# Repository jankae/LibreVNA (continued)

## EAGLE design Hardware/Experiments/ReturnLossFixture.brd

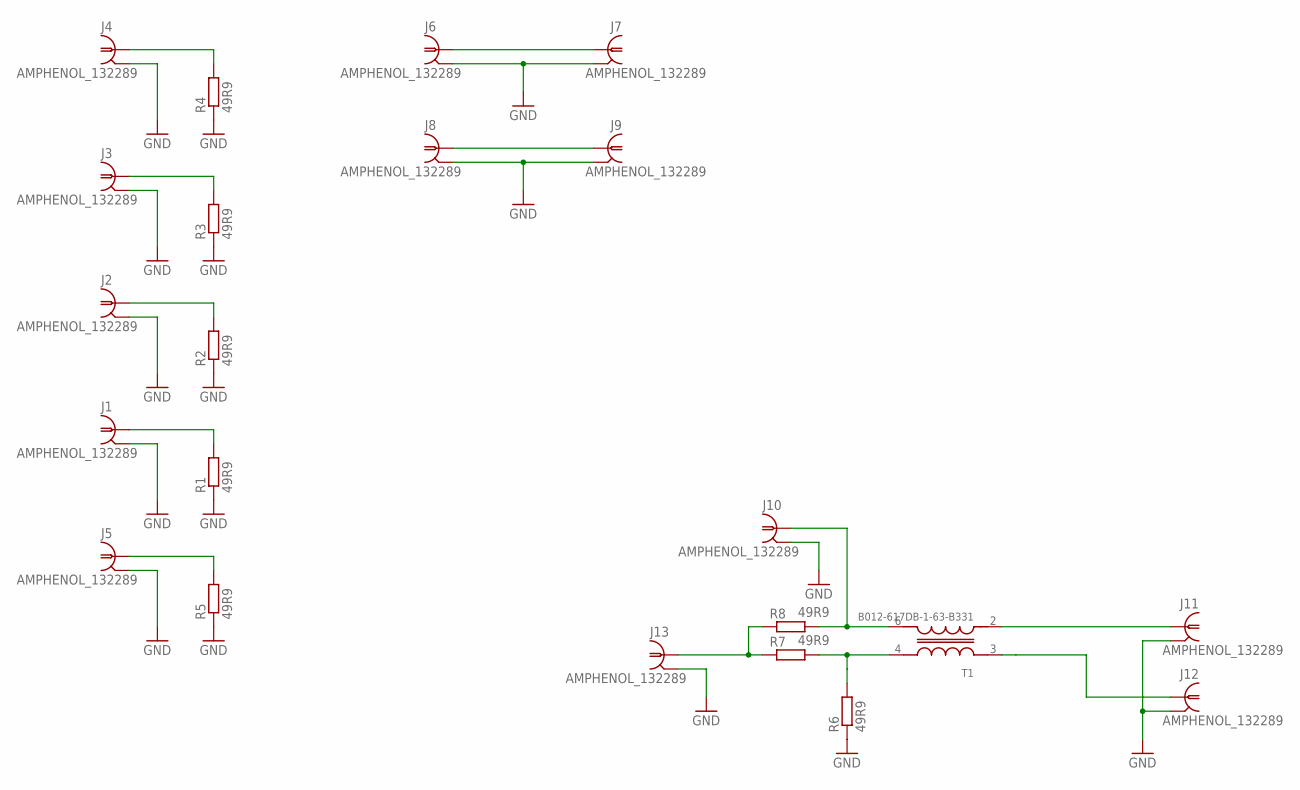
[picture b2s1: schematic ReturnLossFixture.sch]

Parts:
J1, J2, J3, J4, J5, J6, J7, J8, J9, J10, J11, J12, J13: AMPHENOL_132289
R1, R2, R3, R4, R5, R6, R7, R8: 49R9; R0402
T1: B012-617DB-1-63-B331; EASTEVER_BALUN

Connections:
GND: J1.G@1 (2), J1.G@2 (2), J1.G@3 (2), J1.G@4 (2), J2.G@1 (2), J2.G@2 (2), J2.G@3 (2), J2.G@4 (2), J3.G@1 (2), J3.G@2 (2), J3.G@3 (2), J3.G@4 (2), J4.G@1 (2), J4.G@2 (2), J4.G@3 (2), J4.G@4 (2), J5.G@1 (2), J5.G@2 (2), J5.G@3 (2), J5.G@4 (2), J6.G@1 (2), J6.G@2 (2), J6.G@3 (2), J6.G@4 (2), J7.G@1 (2), J7.G@2 (2), J7.G@3 (2), J7.G@4 (2), J8.G@1 (2), J8.G@2 (2), J8.G@3 (2), J8.G@4 (2), J9.G@1 (2), J9.G@2 (2), J9.G@3 (2), J9.G@4 (2), J10.G@1 (2), J10.G@2 (2), J10.G@3 (2), J10.G@4 (2), J11.G@1 (2), J11.G@2 (2), J11.G@3 (2), J11.G@4 (2), J12.G@1 (2), J12.G@2 (2), J12.G@3 (2), J12.G@4 (2), J13.G@1 (2), J13.G@2 (2), J13.G@3 (2), J13.G@4 (2), R1.1, R2.1, R3.1, R4.1, R5.1, R6.1
unnamed: J1.1, R1.2
unnamed: J2.1, R2.2
unnamed: J3.1, R3.2
unnamed: J4.1, R4.2
unnamed: J5.1, R5.2
unnamed: J6.1, J7.1
unnamed: J10.1, R8.2, T1.6 (OUT-)
unnamed: J8.1, J9.1
unnamed: J12.1, T1.3 (IN+)
unnamed: J11.1, T1.2 (IN-)
unnamed: R6.2, R7.2, T1.4 (OUT+)
unnamed: J13.1, R7.1, R8.1

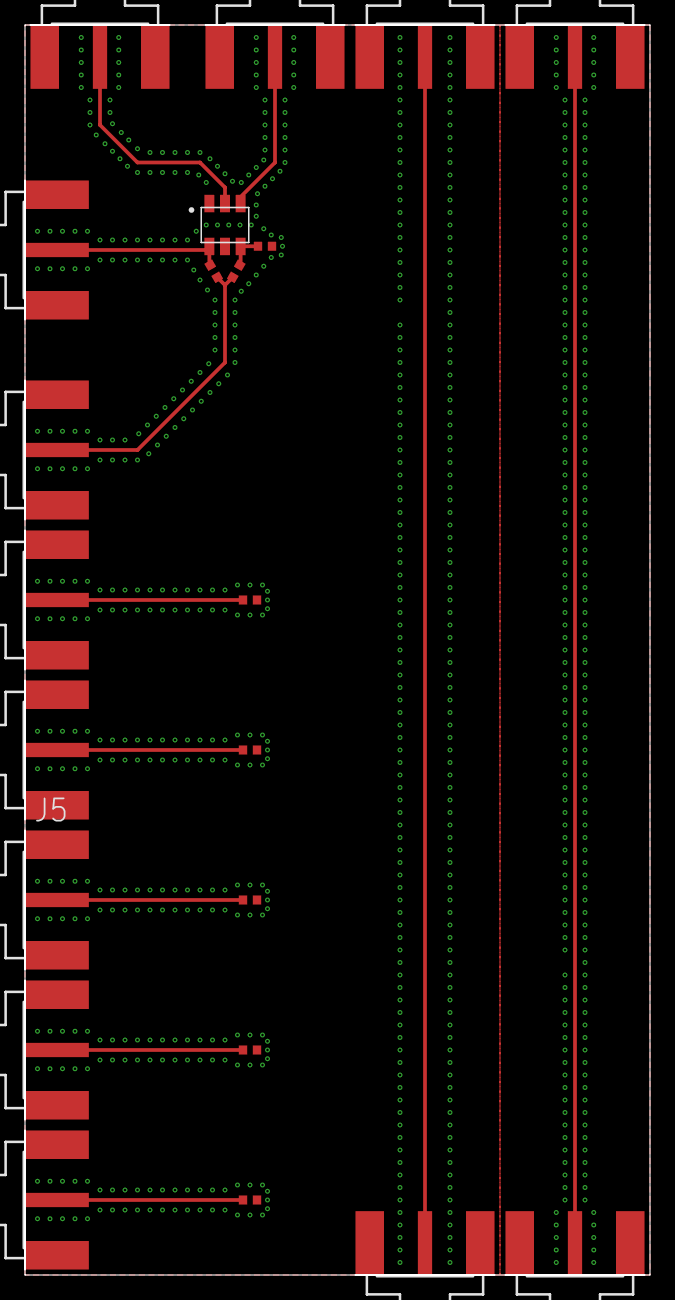
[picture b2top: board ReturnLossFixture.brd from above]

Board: 4 copper layers, 50.0 x 100.0 mm, 22 parts (0 on the bottom side), 13 nets.

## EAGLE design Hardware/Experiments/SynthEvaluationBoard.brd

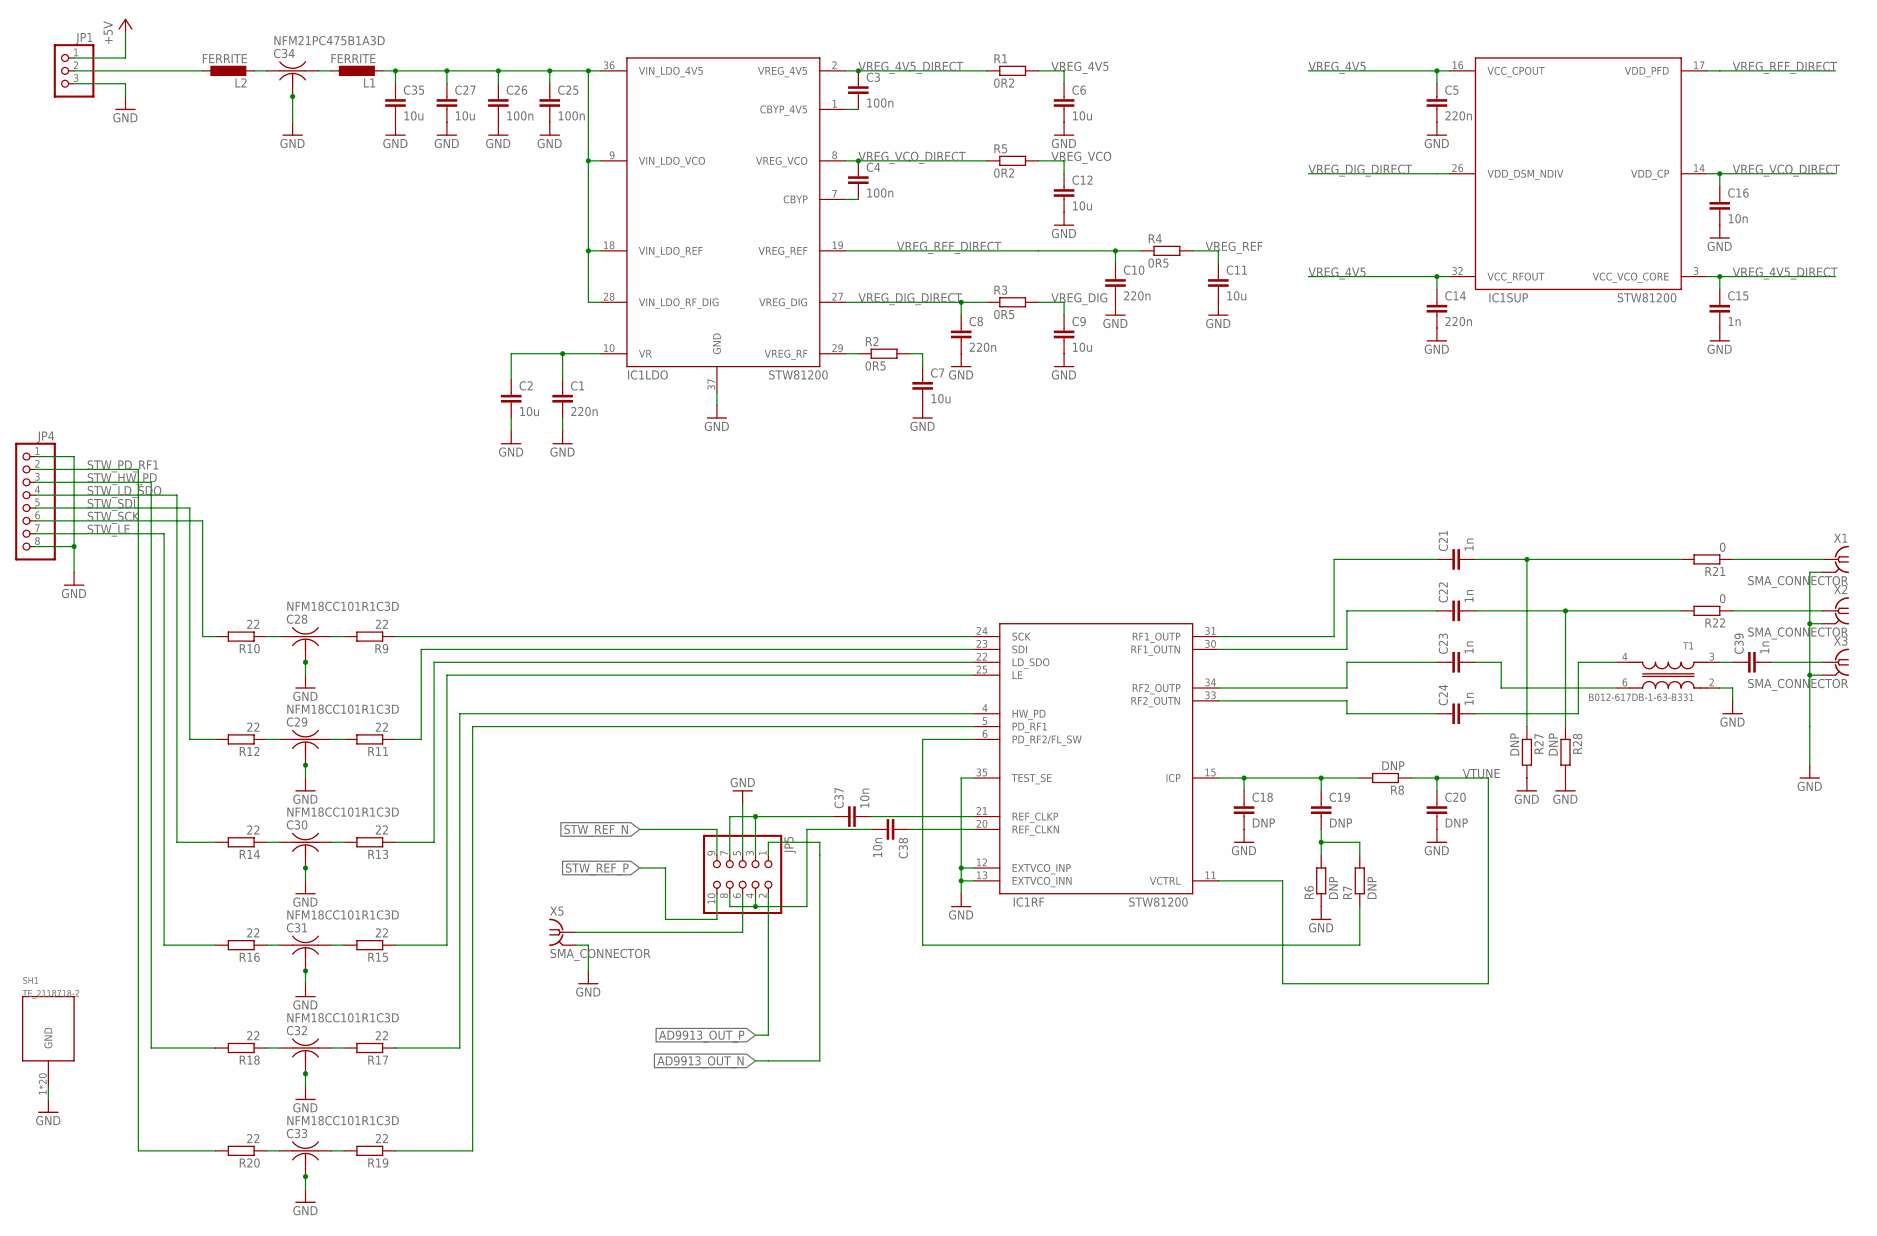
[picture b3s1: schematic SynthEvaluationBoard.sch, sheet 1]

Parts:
C1, C5, C8, C10, C14: 220n; C0402
C2, C6, C7, C9, C11, C12, C27, C35: 10u; C0603
C3, C4, C25, C26: 100n; C0402
C15, C21, C22, C23, C24, C39: 1n; C0402
C16, C37, C38: 10n; C0402
C18, C19, C20: DNP; C0402
C28, C29, C30, C31, C32, C33: NFM18CC101R1C3D; NFM18PC
C34: NFM21PC475B1A3D; NFM21PC
IC1: STW81200; QFN50P600X600X100-37T410N
JP1: PINHD-1X3; 1X03
JP4: PINHD-1X8; 1X08
JP5: PINHD-2X5; 2X05
L1, L2: FERRITE; R0402
R1, R5: 0R2; R0402
R2, R3, R4: 0R5; R0402
R6, R7, R8, R27, R28: DNP; R0402
R9, R10, R11, R12, R13, R14, R15, R16, R17, R18, R19, R20: 22; R0402
R21, R22: 0; R0402
SH1: TE_2118718-2
T1: B012-617DB-1-63-B331; EASTEVER_BALUN
X1, X2, X3, X5: SMA_CONNECTOR; J502-ND-142-0711-821/826

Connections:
+5V: JP1.1; also elsewhere on the board
AD9913_OUT_N: JP5.1; also elsewhere on the board
AD9913_OUT_P: JP5.2; also elsewhere on the board
GND: C1.2, C2.2, C5.2, C6.2, C7.2, C8.2, C9.2, C10.2, C11.2, C12.2, C14.2, C15.2, C16.2, C18.2, C20.2, C25.2, C26.2, C27.2, C28.2, C28.4 (2), C29.2, C29.4 (2), C30.2, C30.4 (2), C31.2, C31.4 (2), C32.2, C32.4 (2), C33.2, C33.4 (2), C34.2, C34.4 (2), C35.2, IC1.12 (EXTVCO_INP), IC1.13 (EXTVCO_INN), IC1.35 (TEST_SE), IC1.37 (GND), JP1.3, JP4.1, JP4.8, JP5.5, R6.1, R27.2, R28.2, SH1.1, SH1.2, SH1.3, SH1.4, SH1.5, SH1.6, SH1.7, SH1.8, SH1.9, SH1.10, SH1.11, SH1.12, SH1.13, SH1.14, SH1.15, SH1.16, SH1.17, SH1.18, SH1.19, SH1.20, T1.2 (IN-), X1.G@1 (2), X1.G@2 (2), X1.G@3 (2), X1.G@4 (2), X2.G@1 (2), X2.G@2 (2), X2.G@3 (2), X2.G@4 (2), X3.G@1 (2), X3.G@2 (2), X3.G@3 (2), X3.G@4 (2), X5.G@1 (2), X5.G@2 (2), X5.G@3 (2), X5.G@4 (2); also elsewhere on the board
unnamed: C1.1, C2.1, IC1.10 (VR)
unnamed: IC1.6 (PD_RF2/FL_SW), R7.1
unnamed: C4.2, IC1.7 (CBYP)
unnamed: C3.2, IC1.1 (CBYP_4V5)
unnamed: C19.2, R6.2, R7.2
unnamed: C18.1, C19.1, IC1.15 (ICP), R8.2
unnamed: C25.1, C26.1, C27.1, C35.1, IC1.9 (VIN_LDO_VCO), IC1.18 (VIN_LDO_REF), IC1.28 (VIN_LDO_RF_DIG), IC1.36 (VIN_LDO_4V5), L1.2
unnamed: IC1.29 (VREG_RF), R2.1
unnamed: C7.1, R2.2
unnamed: C23.1, IC1.34 (RF2_OUTP)
unnamed: C24.1, IC1.33 (RF2_OUTN)
unnamed: C22.1, IC1.30 (RF1_OUTN)
unnamed: C21.1, IC1.31 (RF1_OUTP)
unnamed: C28.1, R10.1
unnamed: C28.3, R9.2
unnamed: C29.1, R12.1
unnamed: C29.3, R11.2
unnamed: C30.1, R14.1
unnamed: C30.3, R13.2
unnamed: C31.1, R16.1
unnamed: C31.3, R15.2
unnamed: C32.1, R18.1
unnamed: C32.3, R17.2
unnamed: C33.1, R20.1
unnamed: C33.3, R19.2
unnamed: IC1.24 (SCK), R9.1
unnamed: IC1.23 (SDI), R11.1
unnamed: IC1.22 (LD_SDO), R13.1
unnamed: IC1.25 (LE), R15.1
unnamed: IC1.4 (HW_PD), R17.1
unnamed: IC1.5 (PD_RF1), R19.1
unnamed: C34.3, L1.1
unnamed: C34.1, L2.2
unnamed: R22.1, X2.1
unnamed: C22.2, R22.2, R28.1
unnamed: C23.2, T1.6 (OUT-)
unnamed: C39.1, T1.3 (IN+)
unnamed: C21.2, R21.2, R27.1
unnamed: R21.1, X1.1
unnamed: C39.2, X3.1
unnamed: JP5.6, X5.1
unnamed: JP1.2, L2.1
unnamed: C24.2, T1.4 (OUT+)
STW81200_CLK_N: C38.1, IC1.20 (REF_CLKN)
STW81200_CLK_P: C37.2, IC1.21 (REF_CLKP)
STW81200_C_N: C38.2, JP5.4, JP5.8
STW81200_C_P: C37.1, JP5.3, JP5.7
STW_HW_PD: JP4.3, R18.2; also elsewhere on the board
STW_LD_SDO: JP4.4, R14.2; also elsewhere on the board
STW_LE: JP4.7, R16.2; also elsewhere on the board
STW_PD_RF1: JP4.2, R20.2; also elsewhere on the board
STW_REF_N: JP5.9; also elsewhere on the board
STW_REF_P: JP5.10; also elsewhere on the board
STW_SCK: JP4.6, R10.2; also elsewhere on the board
STW_SDI: JP4.5, R12.2; also elsewhere on the board
VREG_4V5: C5.1, C6.1, C14.1, IC1.16 (VCC_CPOUT), IC1.32 (VCC_RFOUT), R1.2
VREG_4V5_DIRECT: C3.1, C15.1, IC1.2 (VREG_4V5), IC1.3 (VCC_VCO_CORE), R1.1
VREG_DIG: C9.1, R3.2
VREG_DIG_DIRECT: C8.1, IC1.26 (VDD_DSM_NDIV), IC1.27 (VREG_DIG), R3.1
VREG_REF: C11.1, R4.2
VREG_REF_DIRECT: C10.1, IC1.17 (VDD_PFD), IC1.19 (VREG_REF), R4.1
VREG_VCO: C12.1, R5.2
VREG_VCO_DIRECT: C4.1, C16.1, IC1.8 (VREG_VCO), IC1.14 (VDD_CP), R5.1
VTUNE: C20.1, IC1.11 (VCTRL), R8.1

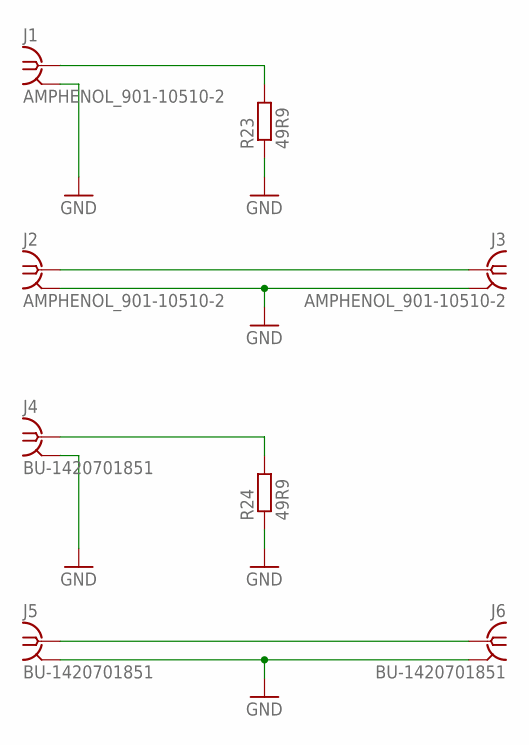
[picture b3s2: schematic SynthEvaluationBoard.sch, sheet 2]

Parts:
J1, J2, J3: AMPHENOL_901-10510-2
J4, J5, J6: BU-1420701851
R23, R24: 49R9; R0402

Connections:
GND: J1.G1 (2), J1.G2 (2), J1.G3 (2), J1.G4 (2), J2.G1 (2), J2.G2 (2), J2.G3 (2), J2.G4 (2), J3.G1 (2), J3.G2 (2), J3.G3 (2), J3.G4 (2), J4.G@1 (2), J4.G@2 (2), J4.G@3 (2), J4.G@4 (2), J5.G@1 (2), J5.G@2 (2), J5.G@3 (2), J5.G@4 (2), J6.G@1 (2), J6.G@2 (2), J6.G@3 (2), J6.G@4 (2), R23.1, R24.1; also elsewhere on the board
unnamed: J1.S (1), R23.2
unnamed: J2.S (1), J3.S (1)
unnamed: J4.1, R24.2
unnamed: J5.1, J6.1

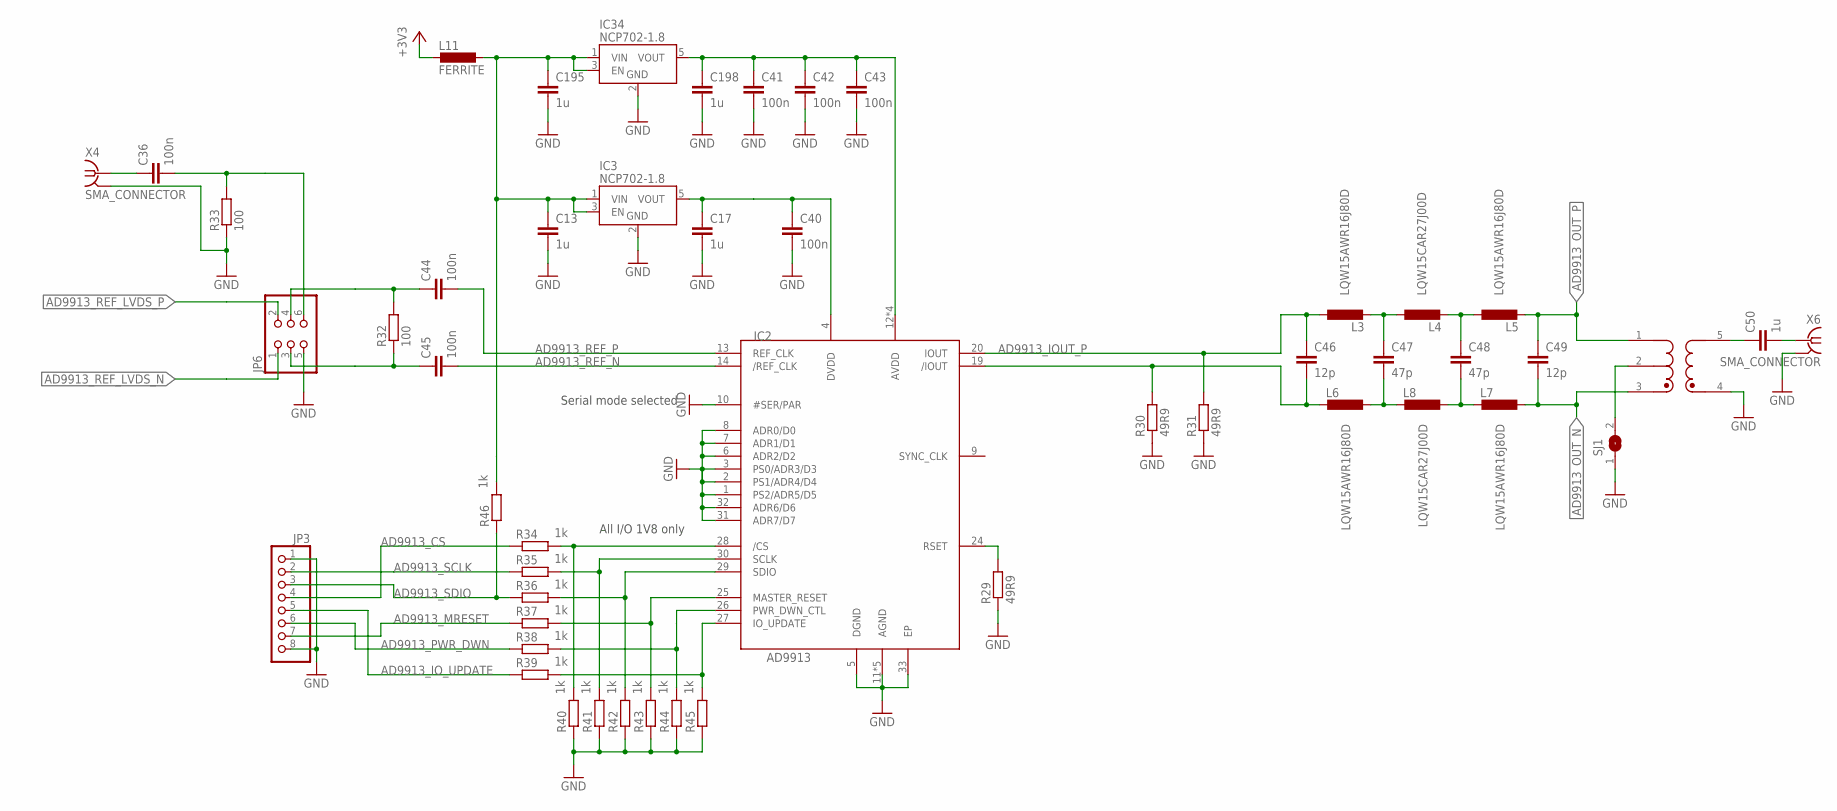
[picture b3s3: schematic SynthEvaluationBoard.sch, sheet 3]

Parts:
B1: ETC1-1T-2; SM-22
C13, C17, C50, C195, C198: 1u; C0402
C36, C40, C41, C42, C43, C44, C45: 100n; C0402
C46, C49: 12p; C0402
C47, C48: 47p; C0402
IC2: AD9913; QFN50P500X500X80-33T310
IC3, IC34: NCP702-1.8; SOT95P240X110-5
JP3: PINHD-1X8; 1X08
JP6: PINHD-2X3; 2X03
L3, L5, L6, L7: LQW15AWR16J80D; L0402
L4, L8: LQW15CAR27J00D; L0402
L11: FERRITE; R0402
R29, R30, R31: 49R9; R0402
R32, R33: 100; R0402
R34, R35, R36, R37, R38, R39, R40, R41, R42, R43, R44, R45, R46: 1k; R0402
SJ1: SJ
X4, X6: SMA_CONNECTOR; J502-ND-142-0711-821/826

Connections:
+3V3: L11.2; also elsewhere on the board
AD9913_CS: JP3.4, R34.1; also elsewhere on the board
AD9913_IOUT_N: C46.2, IC2.19 (/IOUT), L6.2, R30.2
AD9913_IOUT_P: C46.1, IC2.20 (IOUT), L3.1, R31.2
AD9913_IO_UPDATE: JP3.5, R39.1; also elsewhere on the board
AD9913_MRESET: JP3.7, R37.1; also elsewhere on the board
AD9913_OUT_N: B1.3 (SEC_DOT), C49.2, L7.1; also elsewhere on the board
AD9913_OUT_P: B1.1 (SEC), C49.1, L5.2; also elsewhere on the board
AD9913_PWR_DWN: JP3.6, R38.1; also elsewhere on the board
AD9913_REF_IN_N: C45.1, JP6.3, R32.1
AD9913_REF_IN_P: C44.1, JP6.4, R32.2
AD9913_REF_LVDS_N: JP6.1; also elsewhere on the board
AD9913_REF_LVDS_P: JP6.2; also elsewhere on the board
AD9913_REF_N: C45.2, IC2.14 (/REF_CLK)
AD9913_REF_P: C44.2, IC2.13 (REF_CLK)
AD9913_SCLK: JP3.2, R35.1; also elsewhere on the board
AD9913_SDIO: JP3.3, R36.1, R46.1; also elsewhere on the board
GND: B1.4 (PRI_DOT), C13.2, C17.2, C40.2, C41.2, C42.2, C43.2, C195.2, C198.2, IC2.1 (PS2/ADR5/D5), IC2.2 (PS1/ADR4/D4), IC2.3 (PS0/ADR3/D3), IC2.5 (DGND), IC2.6 (ADR2/D2), IC2.7 (ADR1/D1), IC2.8 (ADR0/D0), IC2.10 (#SER/PAR), IC2.11 (AGND), IC2.15 (AGND), IC2.18 (AGND), IC2.21 (AGND), IC2.23 (AGND), IC2.31 (ADR7/D7), IC2.32 (ADR6/D6), IC2.33 (EP), IC3.2 (GND), IC34.2 (GND), JP3.1, JP3.8, JP6.5, R29.1, R30.1, R31.1, R33.1, R40.1, R41.1, R42.1, R43.1, R44.1, R45.1, SJ1.1, X4.G@1 (2), X4.G@2 (2), X4.G@3 (2), X4.G@4 (2), X6.G@1 (2), X6.G@2 (2), X6.G@3 (2), X6.G@4 (2); also elsewhere on the board
unnamed: C13.1, C195.1, IC3.1 (VIN), IC3.3 (EN), IC34.1 (VIN), IC34.3 (EN), L11.1, R46.2
unnamed: C17.1, C40.1, IC2.4 (DVDD), IC3.5 (VOUT)
unnamed: IC2.24 (RSET), R29.2
unnamed: C36.2, JP6.6, R33.2
unnamed: IC2.28 (/CS), R34.2, R40.2
unnamed: IC2.30 (SCLK), R35.2, R41.2
unnamed: IC2.29 (SDIO), R36.2, R42.2
unnamed: IC2.25 (MASTER_RESET), R37.2, R43.2
unnamed: IC2.26 (PWR_DWN_CTL), R38.2, R44.2
unnamed: IC2.27 (IO_UPDATE), R39.2, R45.2
unnamed: C47.1, L3.2, L4.1
unnamed: C47.2, L6.1, L8.2
unnamed: C48.2, L7.2, L8.1
unnamed: C48.1, L4.2, L5.1
unnamed: B1.2 (SEC_CT), SJ1.2
unnamed: C50.2, X6.1
unnamed: C36.1, X4.1
unnamed: B1.5 (PRI), C50.1
unnamed: C41.1, C42.1, C43.1, C198.1, IC2.12 (AVDD), IC2.16 (AVDD), IC2.17 (AVDD), IC2.22 (AVDD), IC34.5 (VOUT)

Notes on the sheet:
Serial mode selected
All I/O 1V8 only

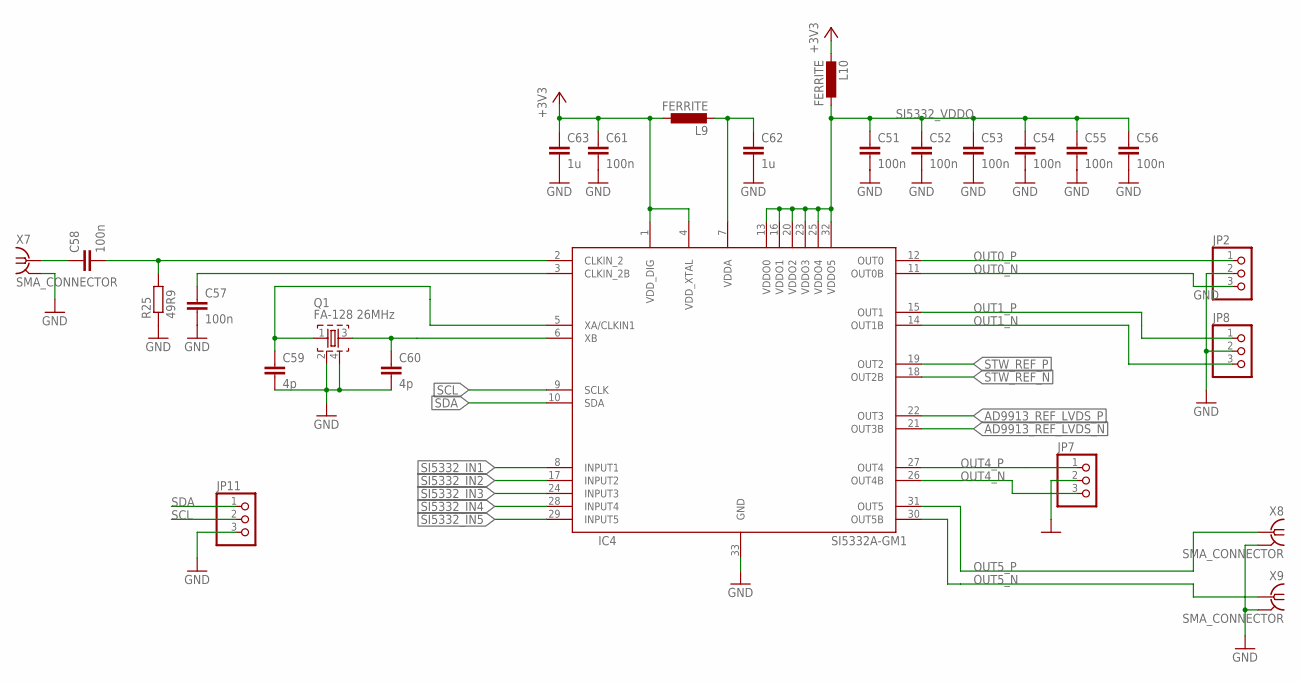
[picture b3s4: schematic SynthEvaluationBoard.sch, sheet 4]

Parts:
C51, C52, C53, C54, C55, C56, C57, C58, C61: 100n; C0402
C59, C60: 4p; C0402
C62, C63: 1u; C0402
IC4: SI5332A-GM1; QFN50P500X500X100-33T345N
JP2, JP7, JP8, JP11: PINHD-1X3; 1X03
L9, L10: FERRITE; R0402
Q1: FA-128 26MHz; FA-128
R25: 49R9; R0402
X7, X8, X9: SMA_CONNECTOR; J502-ND-142-0711-821/826

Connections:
+3V3: C61.1, C63.1, IC4.1 (VDD_DIG), IC4.4 (VDD_XTAL), L9.1, L10.2; also elsewhere on the board
AD9913_REF_LVDS_N: IC4.21 (OUT3B); also elsewhere on the board
AD9913_REF_LVDS_P: IC4.22 (OUT3); also elsewhere on the board
GND: C51.2, C52.2, C53.2, C54.2, C55.2, C56.2, C57.2, C59.2, C60.2, C61.2, C62.2, C63.2, IC4.33 (GND), JP2.2, JP7.2, JP8.2, JP11.3, Q1.2, Q1.4, R25.1, X7.G@1 (2), X7.G@2 (2), X7.G@3 (2), X7.G@4 (2), X8.G@1 (2), X8.G@2 (2), X8.G@3 (2), X8.G@4 (2), X9.G@1 (2), X9.G@2 (2), X9.G@3 (2), X9.G@4 (2); also elsewhere on the board
unnamed: C57.1, IC4.3 (CLKIN_2B)
unnamed: C58.2, IC4.2 (CLKIN_2), R25.2
unnamed: C58.1, X7.1
unnamed: C60.1, IC4.6 (XB), Q1.3
unnamed: C59.1, IC4.5 (XA/CLKIN1), Q1.1
unnamed: C62.1, IC4.7 (VDDA), L9.2
OUT0_N: IC4.11 (OUT0B), JP2.3
OUT0_P: IC4.12 (OUT0), JP2.1
OUT1_N: IC4.14 (OUT1B), JP8.3
OUT1_P: IC4.15 (OUT1), JP8.1
OUT4_N: IC4.26 (OUT4B), JP7.3
OUT4_P: IC4.27 (OUT4), JP7.1
OUT5_N: IC4.30 (OUT5B), X9.1
OUT5_P: IC4.31 (OUT5), X8.1
SCL: IC4.9 (SCLK), JP11.2; also elsewhere on the board
SDA: IC4.10 (SDA), JP11.1; also elsewhere on the board
SI5332_IN1: IC4.8 (INPUT1); also elsewhere on the board
SI5332_IN2: IC4.17 (INPUT2); also elsewhere on the board
SI5332_IN3: IC4.24 (INPUT3); also elsewhere on the board
SI5332_IN4: IC4.28 (INPUT4); also elsewhere on the board
SI5332_IN5: IC4.29 (INPUT5); also elsewhere on the board
SI5332_VDDO: C51.1, C52.1, C53.1, C54.1, C55.1, C56.1, IC4.13 (VDDO0), IC4.16 (VDDO1), IC4.20 (VDDO2), IC4.23 (VDDO3), IC4.25 (VDDO4), IC4.32 (VDDO5), L10.1
STW_REF_N: IC4.18 (OUT2B); also elsewhere on the board
STW_REF_P: IC4.19 (OUT2); also elsewhere on the board

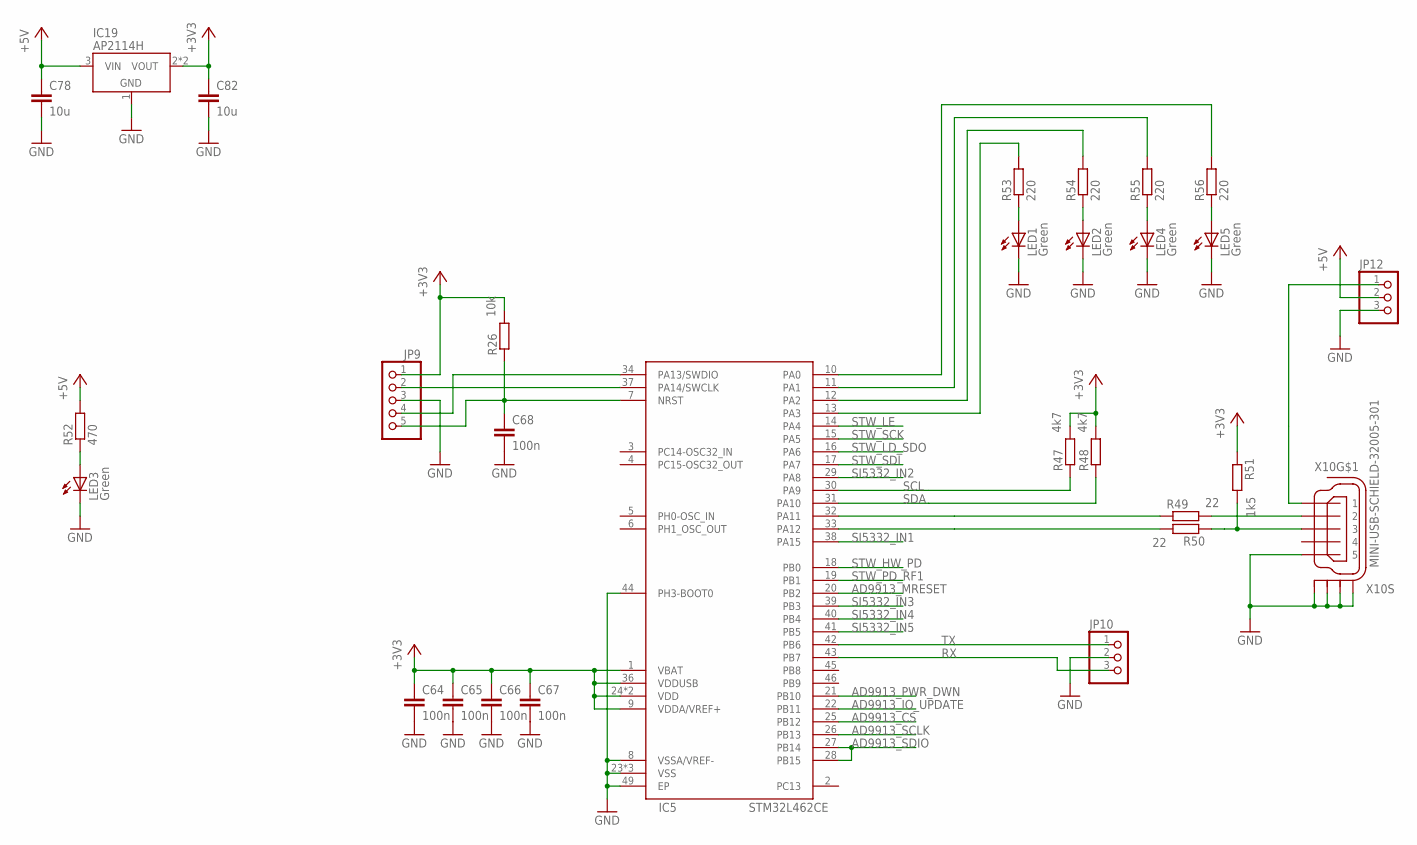
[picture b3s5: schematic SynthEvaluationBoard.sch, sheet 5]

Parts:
C64, C65, C66, C67, C68: 100n; C0402
C78, C82: 10u; C1206
IC5: STM32L462CE; QFN50P700X700X60-49T560N
IC19: AP2114H; SOT230P700X180-4
JP9: PINHD-1X5; 1X05
JP10, JP12: PINHD-1X3; 1X03
LED1, LED2, LED3, LED4, LED5: Green; LED_SML0603
R26: 10k; R0402
R47, R48: 4k7; R0402
R49, R50: 22; R0402
R51: 1k5; R0402
R52: 470; R0402
R53, R54, R55, R56: 220; R0402
X10: MINI-USB-SCHIELD-32005-301; 32005-301

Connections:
+3V3: C64.1, C65.1, C66.1, C67.1, C82.1, IC5.1 (VBAT), IC5.9 (VDDA/VREF+), IC5.24 (VDD), IC5.36 (VDDUSB), IC5.48 (VDD), IC19.2 (VOUT), IC19.4 (VOUT), JP9.1, R26.2, R47.2, R48.2, R51.1; also elsewhere on the board
+5V: C78.1, IC19.3 (VIN), JP12.2, R52.2; also elsewhere on the board
AD9913_CS: IC5.25 (PB12); also elsewhere on the board
AD9913_IO_UPDATE: IC5.22 (PB11); also elsewhere on the board
AD9913_MRESET: IC5.20 (PB2); also elsewhere on the board
AD9913_PWR_DWN: IC5.21 (PB10); also elsewhere on the board
AD9913_SCLK: IC5.26 (PB13); also elsewhere on the board
AD9913_SDIO: IC5.27 (PB14), IC5.28 (PB15); also elsewhere on the board
GND: C64.2, C65.2, C66.2, C67.2, C68.2, C78.2, C82.2, IC5.8 (VSSA/VREF-), IC5.23 (VSS), IC5.35 (VSS), IC5.44 (PH3-BOOT0), IC5.47 (VSS), IC5.49 (EP), IC19.1 (GND), JP9.3, JP10.2, JP12.3, LED1.C, LED2.C, LED3.C, LED4.C, LED5.C, X10.5, X10.M1 (S1), X10.M2 (S2), X10.M3 (S3), X10.M4 (S4); also elsewhere on the board
unnamed: LED3.A, R52.1
unnamed: JP12.1, X10.1
unnamed: LED1.A, R53.1
unnamed: LED2.A, R54.1
unnamed: LED4.A, R55.1
unnamed: IC5.37 (PA14/SWCLK), JP9.2
unnamed: IC5.34 (PA13/SWDIO), JP9.4
unnamed: C68.1, IC5.7 (NRST), JP9.5, R26.1
unnamed: LED5.A, R56.1
unnamed: IC5.13 (PA3), R53.2
unnamed: IC5.12 (PA2), R54.2
unnamed: IC5.11 (PA1), R55.2
unnamed: IC5.10 (PA0), R56.2
unnamed: R49.2, X10.2
unnamed: R50.1, R51.2, X10.3
unnamed: IC5.32 (PA11), R49.1
unnamed: IC5.33 (PA12), R50.2
RX: IC5.43 (PB7), JP10.3
SCL: IC5.30 (PA9), R47.1; also elsewhere on the board
SDA: IC5.31 (PA10), R48.1; also elsewhere on the board
SI5332_IN1: IC5.38 (PA15); also elsewhere on the board
SI5332_IN2: IC5.29 (PA8); also elsewhere on the board
SI5332_IN3: IC5.39 (PB3); also elsewhere on the board
SI5332_IN4: IC5.40 (PB4); also elsewhere on the board
SI5332_IN5: IC5.41 (PB5); also elsewhere on the board
STW_HW_PD: IC5.18 (PB0); also elsewhere on the board
STW_LD_SDO: IC5.16 (PA6); also elsewhere on the board
STW_LE: IC5.14 (PA4); also elsewhere on the board
STW_PD_RF1: IC5.19 (PB1); also elsewhere on the board
STW_SCK: IC5.15 (PA5); also elsewhere on the board
STW_SDI: IC5.17 (PA7); also elsewhere on the board
TX: IC5.42 (PB6), JP10.1

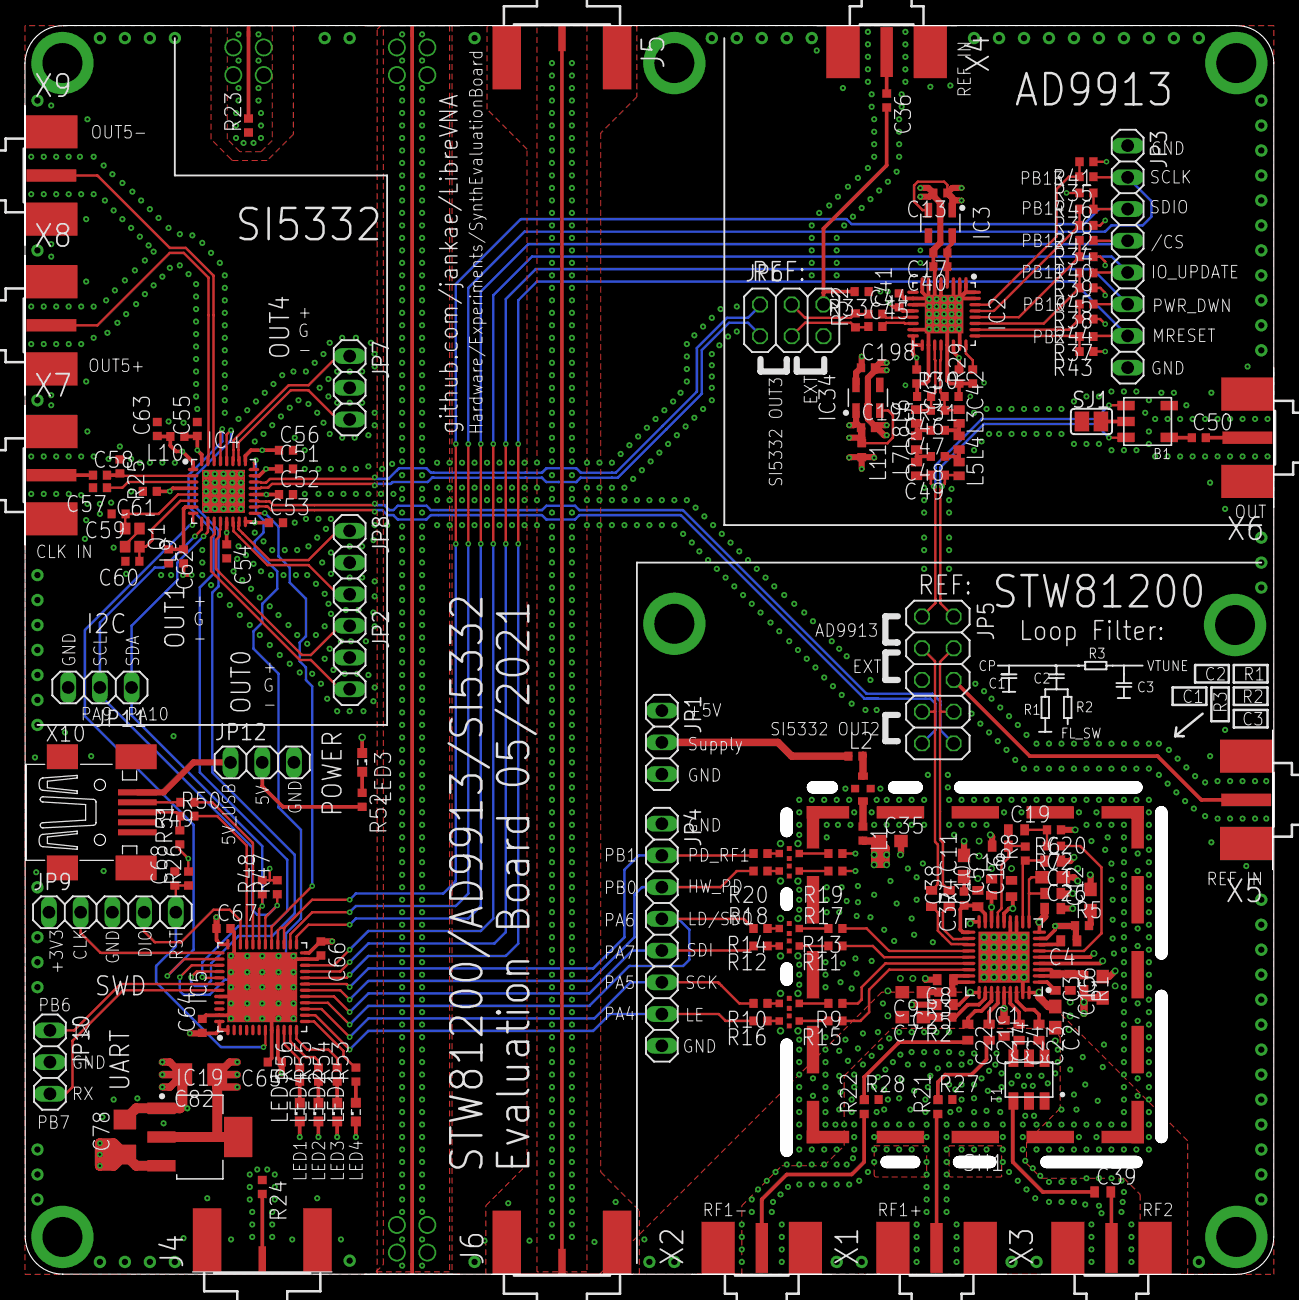
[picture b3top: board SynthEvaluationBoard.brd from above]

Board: 4 copper layers, 100.0 x 100.0 mm, 184 parts (0 on the bottom side), 147 nets.

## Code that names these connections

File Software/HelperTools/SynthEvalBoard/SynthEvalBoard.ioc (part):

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Mcu.Name=STM32L443CCUx
Mcu.Package=UFQFPN48
Mcu.UserName=STM32L443CCUx
PA0.Signal=S_TIM2_CH1
PA1.Signal=S_TIM2_CH2
PA10.Mode=I2C
PA10.Signal=I2C1_SDA
PA11.Mode=Device
PA11.Signal=USB_DM
PA12.Mode=Device
PA12.Signal=USB_DP
PA13\ (JTMS-SWDIO).Mode=Serial_Wire
PA13\ (JTMS-SWDIO).Signal=SYS_JTMS-SWDIO
PA14\ (JTCK-SWCLK).Mode=Serial_Wire
PA14\ (JTCK-SWCLK).Signal=SYS_JTCK-SWCLK
PA15\ (JTDI).GPIOParameters=GPIO_Label
PA15\ (JTDI).GPIO_Label=SI5332_IN1
PA15\ (JTDI).Signal=GPIO_Output
PA2.Signal=S_TIM2_CH3
PA3.Signal=S_TIM2_CH4
PA4.GPIOParameters=GPIO_Label
PA4.GPIO_Label=STW_LE
PA4.Signal=GPIO_Output
PA5.Mode=Full_Duplex_Master
PA5.Signal=SPI1_SCK
PA6.GPIOParameters=GPIO_PuPd
PA6.GPIO_PuPd=GPIO_PULLUP
PA6.Mode=Full_Duplex_Master
PA6.Signal=SPI1_MISO
PA7.Mode=Full_Duplex_Master
PA7.Signal=SPI1_MOSI
PA8.GPIOParameters=GPIO_Label
PA8.GPIO_Label=SI5332_IN2
PA8.Signal=GPIO_Output
PA9.Mode=I2C
PA9.Signal=I2C1_SCL
PB0.GPIOParameters=GPIO_Label
PB0.GPIO_Label=STW_HW_PD
PB0.Signal=GPIO_Output
PB1.GPIOParameters=GPIO_Label
PB1.GPIO_Label=STW_PD_RF1
PB1.Signal=GPIO_Output
PB10.GPIOParameters=GPIO_Label
PB10.GPIO_Label=AD9913_PWR_DWN
PB10.Signal=GPIO_Output
PB11.GPIOParameters=GPIO_Label
PB11.GPIO_Label=AD9913_IO_UPDATE
PB11.Signal=GPIO_Output
PB12.GPIOParameters=GPIO_Label
PB12.GPIO_Label=AD9913_CS
PB12.Signal=GPIO_Output
PB13.Mode=Full_Duplex_Master
PB13.Signal=SPI2_SCK
PB14.Mode=Full_Duplex_Master
PB14.Signal=SPI2_MISO
PB15.Mode=Full_Duplex_Master
PB15.Signal=SPI2_MOSI
PB2.GPIOParameters=GPIO_Label
PB2.GPIO_Label=AD9913_MRESET
PB2.Signal=GPIO_Output
PB3\ (JTDO-TRACESWO).GPIOParameters=GPIO_Label
PB3\ (JTDO-TRACESWO).GPIO_Label=SI5332_IN3
PB3\ (JTDO-TRACESWO).Signal=GPIO_Output
PB4\ (NJTRST).GPIOParameters=GPIO_Label
PB4\ (NJTRST).GPIO_Label=SI5332_IN4
PB4\ (NJTRST).Signal=GPIO_Output
PB5.GPIOParameters=GPIO_Label
PB5.GPIO_Label=SI5332_IN5
PB5.Signal=GPIO_Output
PB6.Mode=Asynchronous
PB6.Signal=USART1_TX
PB7.Mode=Asynchronous
PB7.Signal=USART1_RX
RCC.HSE_VALUE=8000000
RCC.SYSCLKFreq_VALUE=80000000
RCC.SYSCLKSource=RCC_SYSCLKSOURCE_PLLCLK
board=custom

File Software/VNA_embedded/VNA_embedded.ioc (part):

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Mcu.Name=STM32G431C(6-8-B)Ux
Mcu.Package=UFQFPN48
Mcu.UserName=STM32G431CBUx
PA1.GPIOParameters=GPIO_Speed,GPIO_Label
PA1.GPIO_Label=FPGA_AUX1
PA1.GPIO_Speed=GPIO_SPEED_FREQ_VERY_HIGH
PA1.Signal=GPIO_Output
PA10.Mode=EnableDeadBattery
PA10.Signal=UCPD1_DBCC2
PA11.Mode=Device
PA11.Signal=USB_DM
PA12.Mode=Device
PA12.Signal=USB_DP
PA13.Mode=Serial_Wire
PA13.Signal=SYS_JTMS-SWDIO
PA14.Mode=Serial_Wire
PA14.Signal=SYS_JTCK-SWCLK
PA15.Signal=S_TIM2_CH1
PA2.GPIOParameters=GPIO_Speed,GPIO_Label
PA2.GPIO_Label=FPGA_AUX3
PA2.GPIO_Speed=GPIO_SPEED_FREQ_VERY_HIGH
PA2.Signal=GPIO_Output
PA3.GPIOParameters=GPIO_Speed,GPIO_Label
PA3.GPIO_Label=FPGA_AUX2
PA3.GPIO_Speed=GPIO_SPEED_FREQ_VERY_HIGH
PA3.Signal=GPIO_Output
PA4.GPIOParameters=GPIO_Speed,PinState,GPIO_Label
PA4.GPIO_Label=FPGA_CS
PA4.GPIO_Speed=GPIO_SPEED_FREQ_VERY_HIGH
PA4.PinState=GPIO_PIN_SET
PA4.Signal=GPIO_Output
PA5.GPIOParameters=GPIO_Speed
PA5.GPIO_Speed=GPIO_SPEED_FREQ_VERY_HIGH
PA5.Mode=Full_Duplex_Master
PA5.Signal=SPI1_SCK
PA6.GPIOParameters=GPIO_Speed
PA6.GPIO_Speed=GPIO_SPEED_FREQ_VERY_HIGH
PA6.Mode=Full_Duplex_Master
PA6.Signal=SPI1_MISO
PA7.GPIOParameters=GPIO_Speed
PA7.GPIO_Speed=GPIO_SPEED_FREQ_VERY_HIGH
PA7.Mode=Full_Duplex_Master
PA7.Signal=SPI1_MOSI
PA8.GPIOParameters=GPIO_Pu
PA8.GPIO_Pu=GPIO_PULLUP
PA8.Mode=I2C
PA8.Signal=I2C2_SDA
PA9.Mode=EnableDeadBattery
PA9.Signal=UCPD1_DBCC1
PB0.GPIOParameters=GPIO_Speed,PinState,GPIO_Label
PB0.GPIO_Label=FLASH_CS
PB0.GPIO_Speed=GPIO_SPEED_FREQ_VERY_HIGH
PB0.PinState=GPIO_PIN_SET
PB0.Signal=GPIO_Output
PB1.GPIOParameters=GPIO_Label
PB1.GPIO_Label=FPGA_INTR
PB1.Signal=GPXTI1
PB11.Mode=Asynchronous
PB11.Signal=USART3_RX
PB12.GPIOParameters=GPIO_Label
PB12.GPIO_Label=EN_6V
PB12.Signal=GPIO_Output
PB13.GPIOParameters=GPIO_Speed
PB13.GPIO_Speed=GPIO_SPEED_FREQ_VERY_HIGH
PB13.Mode=TX_Only_Simplex_Unidirect_Master
PB13.Signal=SPI2_SCK
PB15.GPIOParameters=GPIO_Speed
PB15.GPIO_Speed=GPIO_SPEED_FREQ_VERY_HIGH
PB15.Mode=TX_Only_Simplex_Unidirect_Master
PB15.Signal=SPI2_MOSI
PB2.GPIOParameters=GPIO_Label
PB2.GPIO_Label=FPGA_PROGRAM_B
PB2.Signal=GPIO_Output
PB3.GPIOParameters=GPIO_Label
PB3.GPIO_Label=FPGA_TRIGGER_IN
PB3.Signal=GPIO_Output
PB4.Mode=Sink_AllSignals
PB4.Signal=UCPD1_CC2
PB5.GPIOParameters=GPIO_Label
PB5.GPIO_Label=FPGA_RESET
PB5.Signal=GPIO_Output
PB6.Mode=Sink_AllSignals
PB6.Signal=UCPD1_CC1
PB9.GPIOParameters=GPIO_Label
PB9.GPIO_Label=FPGA_DONE
PB9.Signal=GPIO_Input
PC10.Mode=Asynchronous
PC10.Signal=USART3_TX
PC11.GPIOParameters=GPIO_PuPd,GPIO_Label
PC11.GPIO_Label=FPGA_TRIGGER_OUT
PC11.GPIO_PuPd=GPIO_PULLDOWN
PC11.Signal=GPIO_Input
PC4.GPIOParameters=GPIO_Pu
PC4.GPIO_Pu=GPIO_PULLUP
PC4.Mode=I2C
PC4.Signal=I2C2_SCL
PF1-OSC_OUT.GPIOParameters=GPIO_Label
PF1-OSC_OUT.GPIO_Label=FPGA_INIT_B
PF1-OSC_OUT.Signal=GPIO_Input
RCC.HSE_VALUE=8000000
RCC.SYSCLKFreq_VALUE=170000000
RCC.SYSCLKSource=RCC_SYSCLKSOURCE_PLLCLK
board=custom

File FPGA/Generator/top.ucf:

CONFIG VCCAUX  = 3.3;
NET "CLK" PERIOD = 62.5 ns HIGH 50%;
NET "MCU_SCK" PERIOD = 25ns HIGH 50%;

NET "ATTENUATION[6]" IOSTANDARD = LVCMOS33;
NET "ATTENUATION[5]" IOSTANDARD = LVCMOS33;
NET "ATTENUATION[4]" IOSTANDARD = LVCMOS33;
NET "ATTENUATION[3]" IOSTANDARD = LVCMOS33;
NET "ATTENUATION[2]" IOSTANDARD = LVCMOS33;
NET "ATTENUATION[1]" IOSTANDARD = LVCMOS33;
NET "ATTENUATION[0]" IOSTANDARD = LVCMOS33;

NET "LEDS[7]" IOSTANDARD = LVCMOS33;
NET "LEDS[6]" IOSTANDARD = LVCMOS33;
NET "LEDS[5]" IOSTANDARD = LVCMOS33;
NET "LEDS[4]" IOSTANDARD = LVCMOS33;
NET "LEDS[3]" IOSTANDARD = LVCMOS33;
NET "LEDS[2]" IOSTANDARD = LVCMOS33;
NET "LEDS[1]" IOSTANDARD = LVCMOS33;
NET "LEDS[0]" IOSTANDARD = LVCMOS33;

NET "AMP_PWDN" IOSTANDARD = LVCMOS33;
NET "CLK" IOSTANDARD = LVCMOS33;
NET "FILT_IN_C2" IOSTANDARD = LVCMOS33;
NET "FILT_IN_C1" IOSTANDARD = LVCMOS33;
NET "FILT_OUT_C2" IOSTANDARD = LVCMOS33;
NET "FILT_OUT_C1" IOSTANDARD = LVCMOS33;
NET "LO1_CE" IOSTANDARD = LVCMOS33;
NET "LO1_LD" IOSTANDARD = LVCMOS33;
NET "LO1_LE" IOSTANDARD = LVCMOS33;
NET "LO1_CLK" IOSTANDARD = LVCMOS33;
NET "LO1_MOSI" IOSTANDARD = LVCMOS33;
NET "LO1_MUX" IOSTANDARD = LVCMOS33;
NET "MCU_AUX1" IOSTANDARD = LVCMOS33;
NET "LO1_RF_EN" IOSTANDARD = LVCMOS33;
NET "SOURCE_RF_EN" IOSTANDARD = LVCMOS33;
NET "SOURCE_MUX" IOSTANDARD = LVCMOS33;
NET "SOURCE_LE" IOSTANDARD = LVCMOS33;
NET "SOURCE_MOSI" IOSTANDARD = LVCMOS33;
NET "SOURCE_LD" IOSTANDARD = LVCMOS33;
NET "SOURCE_CLK" IOSTANDARD = LVCMOS33;
NET "SOURCE_CE" IOSTANDARD = LVCMOS33;
NET "RESET" IOSTANDARD = LVCMOS33;
NET "REF_SDO" IOSTANDARD = LVCMOS33;
NET "REF_SCLK" IOSTANDARD = LVCMOS33;
NET "REF_CONVSTART" IOSTANDARD = LVCMOS33;
NET "PORT2_SDO" IOSTANDARD = LVCMOS33;
NET "PORT2_SCLK" IOSTANDARD = LVCMOS33;
NET "PORT2_CONVSTART" IOSTANDARD = LVCMOS33;
NET "PORT1_SDO" IOSTANDARD = LVCMOS33;
NET "PORT1_SCLK" IOSTANDARD = LVCMOS33;
NET "PORT1_CONVSTART" IOSTANDARD = LVCMOS33;
NET "MCU_SCK" IOSTANDARD = LVCMOS33;
NET "MCU_NSS" IOSTANDARD = LVCMOS33;
NET "MCU_MISO" IOSTANDARD = LVCMOS33;
NET "MCU_MOSI" IOSTANDARD = LVCMOS33;
NET "MCU_INTR" IOSTANDARD = LVCMOS33;
NET "MCU_AUX2" IOSTANDARD = LVCMOS33;
NET "MCU_AUX3" IOSTANDARD = LVCMOS33;

NET "PORT1_SCLK" SLEW = FAST;
NET "PORT2_SCLK" SLEW = FAST;
NET "REF_SCLK" SLEW = FAST;

NET "ATTENUATION[6]" LOC = P9;
NET "ATTENUATION[5]" LOC = P10;
NET "ATTENUATION[4]" LOC = P11;
NET "ATTENUATION[3]" LOC = P12;
NET "ATTENUATION[2]" LOC = P14;
NET "ATTENUATION[1]" LOC = P15;
NET "ATTENUATION[0]" LOC = P16;
NET "LEDS[0]" LOC = P87;
NET "LEDS[1]" LOC = P92;
NET "LEDS[2]" LOC = P93;
NET "LEDS[3]" LOC = P88;
NET "LEDS[4]" LOC = P85;
NET "LEDS[5]" LOC = P84;
NET "LEDS[6]" LOC = P83;
NET "LEDS[7]" LOC = P82;
NET "AMP_PWDN" LOC = P8;
NET "BAND_SELECT_HIGH" LOC = P21;
NET "BAND_SELECT_LOW" LOC = P17;
NET "CLK" LOC = P50;
NET "FILT_IN_C1" LOC = P26;
NET "FILT_IN_C2" LOC = P24;
NET "FILT_OUT_C1" LOC = P22;
NET "FILT_OUT_C2" LOC = P23;
NET "LO1_CE" LOC = P45;
NET "LO1_CLK" LOC = P48;
NET "LO1_LD" LOC = P56;
NET "LO1_LE" LOC = P46;
NET "LO1_MOSI" LOC = P47;
NET "LO1_MUX" LOC = P51;
NET "LO1_RF_EN" LOC = P55;
NET "MCU_AUX1" LOC = P78;
NET "MCU_AUX2" LOC = P75;
NET "MCU_AUX3" LOC = P74;
NET "MCU_INTR" LOC = P59;
NET "MCU_MISO" LOC = P62;
NET "MCU_MOSI" LOC = P61;
NET "MCU_NSS" LOC = P67;
NET "MCU_SCK" LOC = P66;
NET "MCU_SCK" CLOCK_DEDICATED_ROUTE = FALSE;

# PlanAhead Generated physical constraints 

NET "PORT1_CONVSTART" LOC = P139;
NET "PORT1_MIX1_EN" LOC = P141;
NET "PORT1_MIX2_EN" LOC = P140;
NET "PORT1_SCLK" LOC = P137;
NET "PORT1_SDO" LOC = P138;
NET "PORT1_SELECT" LOC = P142;
NET "PORT2_CONVSTART" LOC = P44;
NET "PORT2_MIX1_EN" LOC = P58;
NET "PORT2_MIX2_EN" LOC = P57;
NET "PORT2_SCLK" LOC = P41;
NET "PORT2_SDO" LOC = P43;
NET "PORT2_SELECT" LOC = P40;
NET "PORT_SELECT1" LOC = P6;
NET "PORT_SELECT2" LOC = P7;
NET "REF_CONVSTART" LOC = P5;
NET "REF_MIX1_EN" LOC = P144;
NET "REF_MIX2_EN" LOC = P143;
NET "REF_SCLK" LOC = P1;
NET "REF_SDO" LOC = P2;
NET "RESET" LOC = P79;
NET "SOURCE_CE" LOC = P27;
NET "SOURCE_CLK" LOC = P32;
NET "SOURCE_LD" LOC = P35;
NET "SOURCE_LE" LOC = P29;
NET "SOURCE_MOSI" LOC = P30;
NET "SOURCE_MUX" LOC = P33;
NET "SOURCE_RF_EN" LOC = P34;

# PlanAhead Generated IO constraints 

NET "BAND_SELECT_HIGH" IOSTANDARD = LVCMOS33;
NET "BAND_SELECT_LOW" IOSTANDARD = LVCMOS33;
NET "PORT1_MIX1_EN" IOSTANDARD = LVCMOS33;
NET "PORT1_MIX2_EN" IOSTANDARD = LVCMOS33;
NET "PORT1_SELECT" IOSTANDARD = LVCMOS33;
NET "PORT2_MIX1_EN" IOSTANDARD = LVCMOS33;
NET "PORT2_MIX2_EN" IOSTANDARD = LVCMOS33;
NET "PORT2_SELECT" IOSTANDARD = LVCMOS33;
NET "PORT_SELECT1" IOSTANDARD = LVCMOS33;
NET "PORT_SELECT2" IOSTANDARD = LVCMOS33;
NET "REF_MIX1_EN" IOSTANDARD = LVCMOS33;
NET "REF_MIX2_EN" IOSTANDARD = LVCMOS33;

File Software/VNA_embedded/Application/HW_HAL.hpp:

#pragma once

#include "stm.hpp"
#include "Si5351C.hpp"
#include "max2871.hpp"
#include "main.h"
#include "Flash.hpp"

extern I2C_HandleTypeDef hi2c2;
extern SPI_HandleTypeDef hspi1;

namespace HWHAL {

extern Si5351C Si5351;
extern MAX2871 Source;
extern MAX2871 LO1;
extern Flash flash;

// Mapping of the Si5351 channels to PLLs/Mixers
namespace SiChannel {
	enum {
		Source = 3,
		LO1 = 5,
		Port2LO2 = 4,
		RefLO2 = 1,
		Port1LO2 = 2,
		LowbandSource = 0,
		ReferenceOut = 6,
		FPGA = 7,
	};
}

}
